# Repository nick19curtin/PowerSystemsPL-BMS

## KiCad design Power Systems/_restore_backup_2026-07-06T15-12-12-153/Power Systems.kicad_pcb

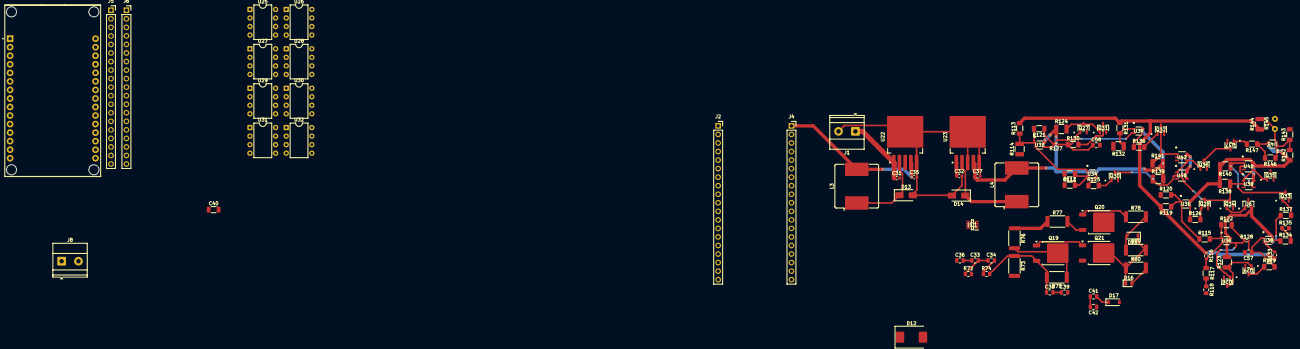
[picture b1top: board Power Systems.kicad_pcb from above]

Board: 2 copper layers, 113 parts (0 on the bottom side), 90 nets.

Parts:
C31, C32: 680uF; C_0603_1608Metric
C33, C34, C36, C38, C39, C41, C42: 0.1uF; C_0805_2012Metric
C35, C37: 220uF; C_0603_1608Metric
C40: 4.7uF; C_1206_3216Metric
C57, C58: 100nF; C_0805_2012Metric_Pad1.18x1.45mm_HandSolder
D12: SMCJ45A; D_SMC
D13, D14: SS34; D_SMA
D15: 1.25V; D_SOD-123
D16: D_Zener; D_0805_2012Metric
D17: D; D_SOD-123
IC1: INA296A3IDDFR; SOT65P280X110-8N
J1, J8: Conn_01x02; TerminalBlock_Phoenix_MKDS-1,5-2_1x02_P5.00mm_Horizontal
J2, J4, J5, J6: Conn_01x19; PinSocket_1x19_P2.54mm_Vertical
L3, L4: 33uH; L_Bourns_SRR1208_12.7x12.7mm
Q19, Q21: IRLR7843; TO-252-2
Q20: PMOS; TO-252-2
Q26, Q27, Q28, Q29, Q30, Q31, Q32, Q33, Q34, Q35, Q36, Q37: 2N7002; SOT-23TO-236_318-08_ONS-M
R72, R74: 100; R_0805_2012Metric
R73: 3.3M; R_2512_6332Metric
R75, R79, R80: 1M; R_2512_6332Metric
R76, R77: 10k; R_2512_6332Metric
R78: 1k; R_2512_6332Metric
R111: 1.5k; R_1206_3216Metric_Pad1.30x1.75mm_HandSolder
R112: 1.6k; R_1206_3216Metric_Pad1.30x1.75mm_HandSolder
R113, R131: 18k; R_1206_3216Metric_Pad1.30x1.75mm_HandSolder
R114, R123, R124, R132, R138, R139, R140, R141, R144: 10k; R_1210_3225Metric_Pad1.30x2.65mm_HandSolder
R115: 124K; R_1206_3216Metric_Pad1.30x1.75mm_HandSolder
R116, R133: 30k; R_0603_1608Metric_Pad0.98x0.95mm_HandSolder
R117, R134: 68k; R_1206_3216Metric_Pad1.30x1.75mm_HandSolder
R118, R135: 2k; R_0805_2012Metric_Pad1.20x1.40mm_HandSolder
R119: 50k; R_1206_3216Metric_Pad1.30x1.75mm_HandSolder
R120: 47k; R_1206_3216Metric_Pad1.30x1.75mm_HandSolder
R121: 390k; R_1206_3216Metric_Pad1.30x1.75mm_HandSolder
R122: 2Meg; R_1206_3216Metric_Pad1.30x1.75mm_HandSolder
R125, R126, R129, R130, R136, R137, R147: 220; R_1206_3216Metric_Pad1.30x1.75mm_HandSolder
R127, R128: 1k; R_0402_1005Metric_Pad0.72x0.64mm_HandSolder
R142: 13k; R_1206_3216Metric_Pad1.30x1.75mm_HandSolder
R143: 4.3k; R_1206_3216Metric_Pad1.30x1.75mm_HandSolder
R145: R_Variable; MF52C1103F3380_Thermistor-317-1376-ND-MF52C1103F3380
R146: 110k; R_1206_3216Metric_Pad1.30x1.75mm_HandSolder
U6: DS1812R-10+T&R; 21-0051H_MXM-M
U21: ESP32-DEVKIT-V1; MODULE_ESP32_DEVKIT_V1
U22: LM2596S-3.3; TO-263-5_TabPin3
U23: LM2596S-5; TO-263-5_TabPin3
U25, U26: LM358; DIP-8_W7.62mm
U27, U28, U29, U30, U31, U32: LM2903; DIP-8_W7.62mm
U33, U34, U35, U36, U37, U38, U43: LMV331; SC70-5_DCK_TEX-M
U39, U40, U41, U42: SN74AHC1G00DBVR; DBV5-M

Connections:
3.3v: C35.1, IC1.6 (VS), IC1.7 (REF1), J4.1, J6.1, L3.2, R111.2, R113.2, R116.1, R119.2, R131.1, R133.1, R144.1, U21.1 (3V3), U22.4 (FB)
5v: C37.1, L4.2, R76.1, R77.1, R123.2, R124.1, R138.2, R139.2, R140.2, R141.2, R142.1, U6.2 (VCC), U23.4 (FB), U33.5 (V+), U34.5 (V+), U35.5 (V+), U36.5 (V+), U37.5 (V+), U38.5 (V+), U39.5 (VCC), U40.5 (VCC), U41.5 (VCC), U42.5 (VCC), U43.5 (V+)
+12.6V: C31.2, C32.2, C33.1, C35.2, C36.2, C37.2, C39.2, C40.1, C40.2, C42.1, C57.2, C58.2, D12.1 (A1), D13.2 (A), D14.2 (A), D16.2 (A), D17.2 (A), IC1.2 (GND), IC1.3 (REF2), J1.2, J4.19, J6.19, J8.2, Q20.2 (G), Q21.3 (S), Q26.2 (S), Q27.2 (S), Q28.2 (S), Q29.2 (S), Q30.2 (S), Q31.2 (S), Q32.2 (S), Q33.2 (S), Q34.2 (S), Q35.2 (S), Q36.2 (S), Q37.2 (S), R72.2, R73.2, R80.2, R112.1, R114.1, R118.2, R120.1, R132.2, R135.2, R143.2, R145.2, U6.3 (GND), U21.2 (GND), U21.29 (GND), U22.3 (GND), U22.5 (~ON/OFF), U23.3 (GND), U23.5 (~ON/OFF), U25.4 (V-), U26.4 (V-), U27.4 (V-), U28.4 (V-), U29.4 (V-), U30.4 (V-), U31.4 (V-), U32.4 (V-), U33.2 (V-), U34.2 (V-), U35.2 (V-), U36.2 (V-), U37.2 (V-), U38.2 (V-), U39.3 (GND), U40.3 (GND), U41.3 (GND), U42.3 (GND), U43.2 (V-)
+15V: U25.8 (V+), U26.8 (V+), U27.8 (V+), U28.8 (V+), U29.8 (V+), U30.8 (V+), U31.8 (V+), U32.8 (V+)
/ALERT: J2.10, J5.10, U21.4 (D2)
/CHG_GATE: Q20.3 (S), R77.2
/Current/CHG_GATE: Q36.3 (D), Q37.3 (D)
/Current/CRESET: Q28.3 (D), Q30.3 (D), Q34.3 (D), R138.1, R139.1, U39.2 (B), U40.2 (B)
/Current/CSET: Q32.3 (D), R141.1, U42.1 (A)
/Current/DSET: Q33.3 (D), R140.1, U41.1 (A)
/Current/ISense_Out: R115.1, U33.3 (-), U34.1 (+), U35.3 (-)
/Current/V_TempSense: R144.2, R145.1, U43.3 (-)
/DSG_GATE: Q19.2 (G), R75.1, R76.2
/LOAD+: C31.1, C32.1, C41.2, D17.1 (K), J1.1, J8.1, U22.1 (VIN), U23.1 (VIN)
/SCL: J2.1, J5.1, U21.11 (D21)
/SDA: J4.10, J6.10, U21.14 (D22)
/SRN: C33.2, C34.1, IC1.1 (IN-), R72.1
/SRP: C34.2, C36.1, IC1.8 (IN+), R74.1
/Voltage/CELL 1: U26.6 (-), U29.6 (-)
/Voltage/CHG_GATE: U27.7, U28.7, U29.7, U30.7, U31.7, U32.7
/Voltage/OUT2: U26.7, U28.6 (-)
/Voltage/OUT3: U25.7, U27.6 (-)
/Voltage/VREF: U27.5 (+), U28.5 (+), U29.5 (+)
/Voltage/VREF_UV: U30.6 (-), U31.6 (-), U32.6 (-)
unnamed: C38.2, C39.1
unnamed: C41.1, C42.2
unnamed: D13.1 (K), L3.1, U22.2 (OUT)
unnamed: D14.1 (K), L4.1, U23.2 (OUT)
unnamed: D15.2 (A), R78.2, R79.1
unnamed: D15.1 (K), D16.1 (K), Q21.2 (G), R79.2, R80.1
unnamed: J5.2, U21.10 (D19)
unnamed: J5.3, U21.9 (D18)
unnamed: J5.4, U21.3 (D15)
unnamed: J5.5, U21.26 (D14)
unnamed: J5.6, U21.28 (D13)
unnamed: J5.7, U21.27 (D12)
unnamed: J5.8, U21.8 (D5)
unnamed: J5.9, U21.5 (D4)
unnamed: J5.15, U21.18 (VN)
unnamed: J5.16, U21.17 (VP)
unnamed: J5.18, U21.16 (EN)
unnamed: J5.19, U21.30 (VIN)
unnamed: J6.4, U21.12 (RX0)
unnamed: J6.5, U21.13 (TX0)
unnamed: J6.7, U21.6 (RX2)
unnamed: J6.8, U21.7 (TX2)
unnamed: J6.11, U21.15 (D23)
unnamed: J6.12, U21.23 (D25)
unnamed: J6.13, U21.24 (D26)
unnamed: J6.14, U21.25 (D27)
unnamed: J6.15, U21.21 (D32)
unnamed: J6.16, U21.22 (D33)
unnamed: J6.17, U21.20 (D35)
unnamed: J6.18, U21.19 (D34)
unnamed: Q19.1 (D), Q21.1 (D)
unnamed: C38.1, Q19.3 (S), R73.1, R74.2, R75.2
unnamed: Q20.1 (D), R78.1
unnamed: Q26.3 (D), Q29.1 (G), R123.1
unnamed: Q26.1 (G), R122.2, R128.1, U36.4
unnamed: Q27.3 (D), Q31.1 (G), R124.2
unnamed: Q27.1 (G), R121.1, R127.2, U33.4
unnamed: Q28.1 (G), R126.2
unnamed: Q29.3 (D), R129.1
unnamed: Q30.1 (G), R125.2
unnamed: Q31.3 (D), R130.2
unnamed: Q32.1 (G), R136.2
unnamed: Q33.1 (G), R137.2
unnamed: Q34.1 (G), U6.1 (RST)
unnamed: Q35.1 (G), U39.1 (A), U41.4 (Y)
unnamed: Q36.1 (G), U40.1 (A), U42.4 (Y)
unnamed: Q37.1 (G), R147.2
unnamed: R117.2, R118.1
unnamed: R125.1, U34.4
unnamed: R126.1, U35.4
unnamed: R134.2, R135.1
unnamed: R136.1, U37.4
unnamed: R137.1, U38.4
unnamed: R146.2, R147.1, U43.4
unnamed: R113.1, R114.2, R121.2, U33.1 (+)
unnamed: R111.1, R112.2, U34.3 (-)
unnamed: R119.1, R120.2, U35.1 (+)
unnamed: R115.2, R122.1, U36.1 (+)
unnamed: R116.2, R117.1, U36.3 (-)
unnamed: R131.2, R132.1, U37.1 (+)
unnamed: C58.1, R127.1, R130.1, U37.3 (-)
unnamed: C57.1, R128.2, R129.2, U38.1 (+)
unnamed: R133.2, R134.1, U38.3 (-)
unnamed: U39.4 (Y), U41.2 (B)
unnamed: U40.4 (Y), U42.2 (B)
unnamed: R142.2, R143.1, R146.1, U43.1 (+)

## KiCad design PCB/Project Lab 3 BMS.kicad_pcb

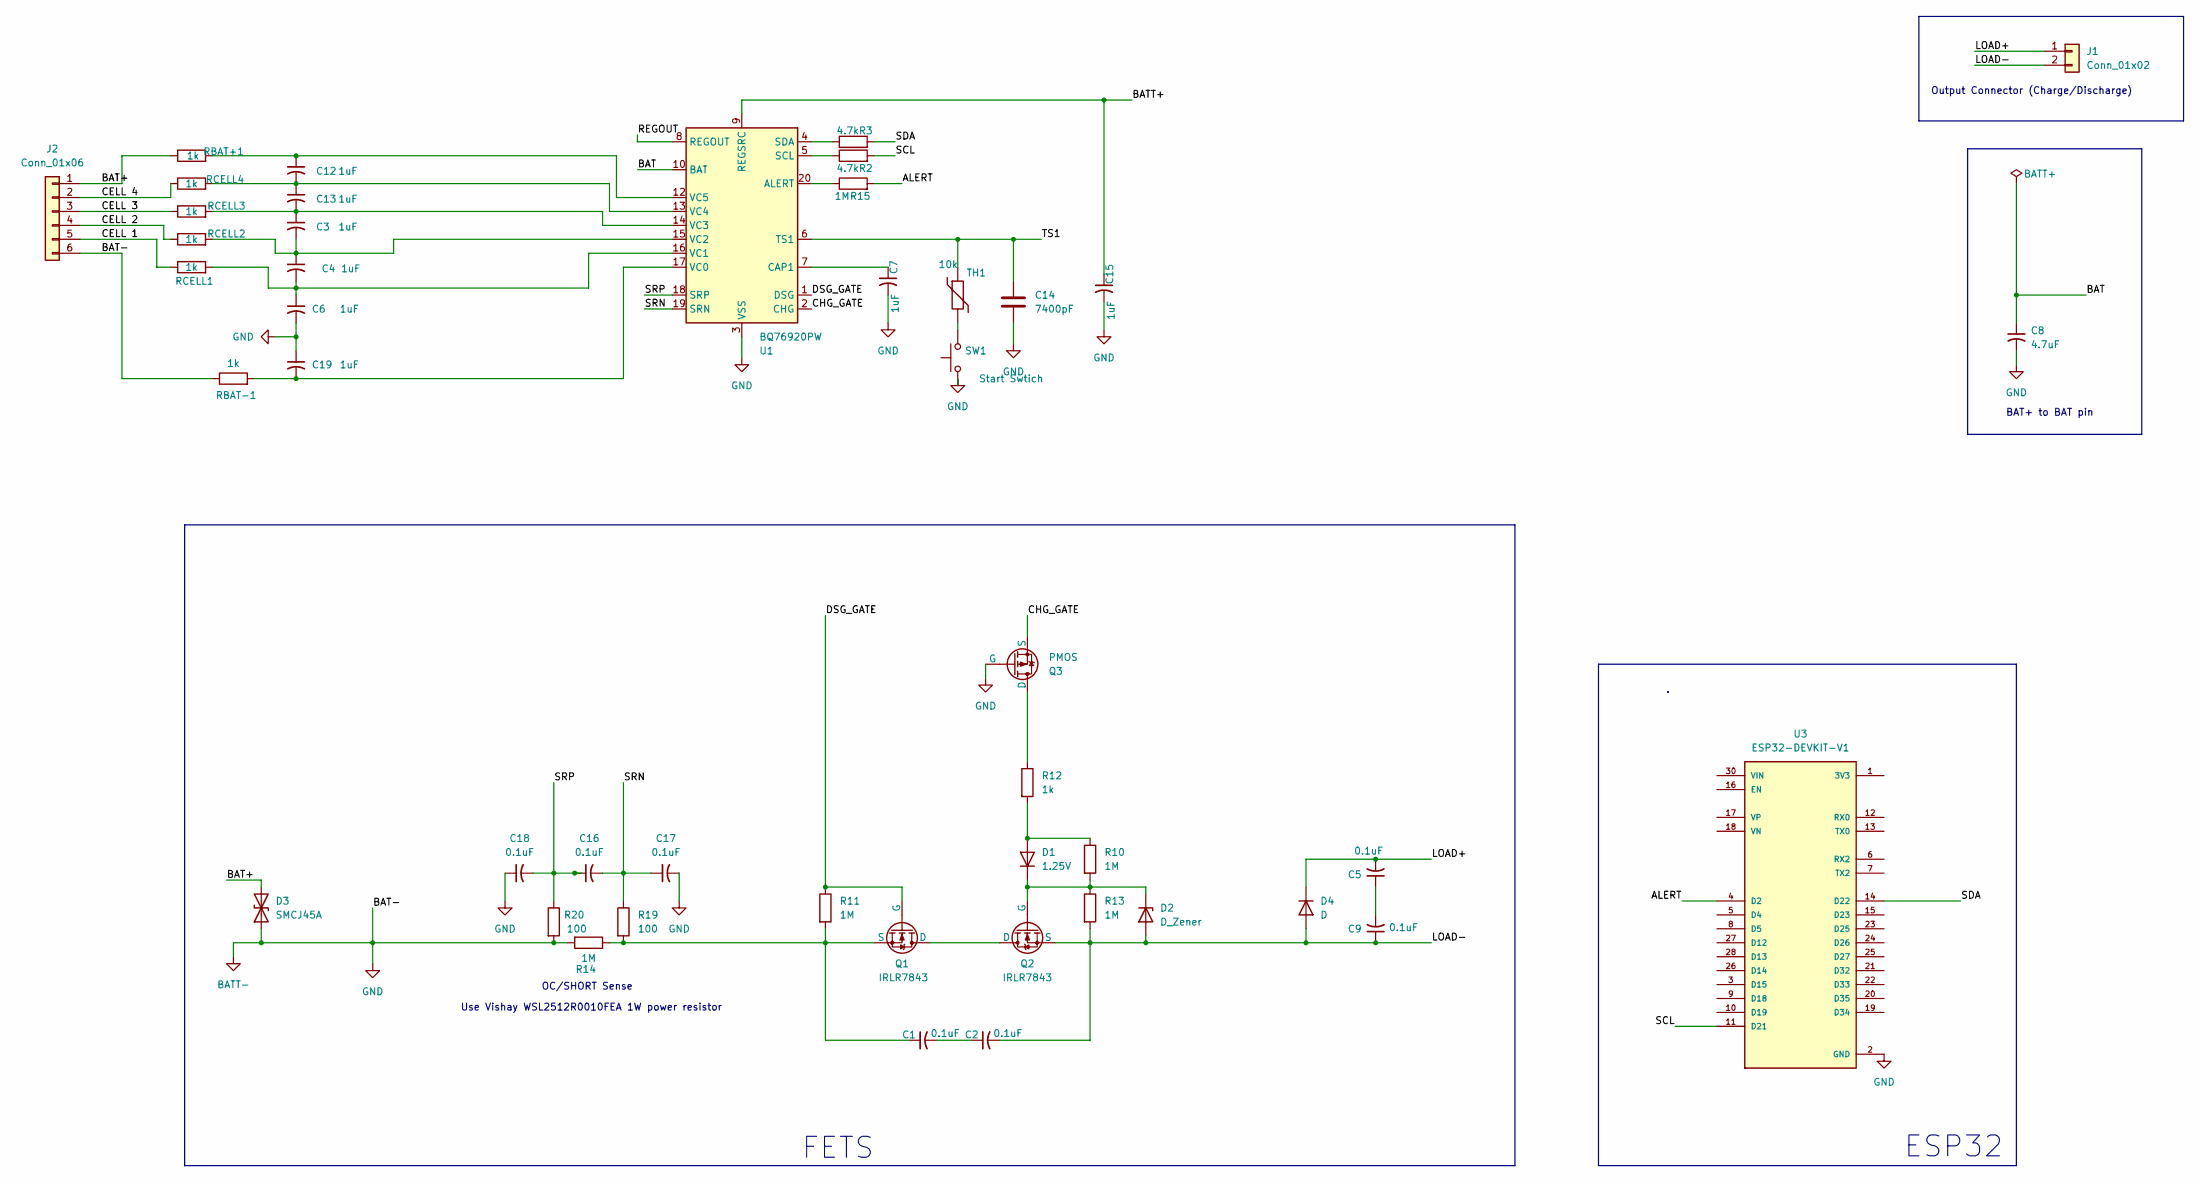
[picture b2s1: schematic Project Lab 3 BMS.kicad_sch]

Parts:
C1, C2, C5, C9, C16, C17, C18: 0.1uF; C_0805_2012Metric
C3, C4, C6, C7, C12, C13, C15, C19: 1uF; C_0805_2012Metric
C8: 4.7uF; C_1206_3216Metric
C14: 7400pF; C_0805_2012Metric
D1: 1.25V; D_SOD-123
D2: D_Zener; D_0201_0603Metric
D3: SMCJ45A; D_SMC
D4: D; D_SOD-123
J1: Conn_01x02; TerminalBlock_Phoenix_MKDS-1,5-2_1x02_P5.00mm_Horizontal
J2: Conn_01x06; JST_XH_B6B-XH-A_1x06_P2.50mm_Vertical
Q1, Q2: IRLR7843; TO-252-2
Q3: PMOS; TO-252-2
R2, R3: 4.7k; C_0805_2012Metric
R10, R11, R13, R14, R15: 1M; R_2512_6332Metric
R12: 1k; R_2512_6332Metric
R19, R20: 100; R_0805_2012Metric
RBAT+1: 1k; R_0805_2012Metric
RBAT-1: 1k; R_0805_2012Metric
RCELL1, RCELL2, RCELL3: 1k; C_0805_2012Metric
RCELL4: 1k; R_0805_2012Metric
SW1: Start Swtich; SW_SPST_PTS645Sx43SMTR92
TH1: 10k; R_0805_2012Metric
U1: BQ76920PW; TSSOP-20_4.4x6.5mm_P0.65mm
U3: ESP32-DEVKIT-V1; MODULE_ESP32_DEVKIT_V1; PARTREV N/A

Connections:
/<NO NET>: J2.5, RCELL1.1
/ALERT: R15.2, U3.4 (D2)
/BAT: C8.1, U1.10 (BAT)
/BAT+: D3.2 (A2), J2.1, RBAT+1.1
/BATT+: C15.1, U1.9 (REGSRC)
/CELL 2: J2.4, RCELL2.1
/CELL 3: J2.3, RCELL3.1
/CELL 4: J2.2, RCELL4.1
/CHG_GATE: Q3.3 (S), U1.2 (CHG)
/DSG_GATE: Q1.2 (G), R11.1, U1.1 (DSG)
/LOAD+: C5.2, D4.1 (K), J1.1
/LOAD-: C2.2, C9.1, D2.2 (A), D4.2 (A), J1.2, Q2.3 (S), R13.2
/REGOUT: U1.8 (REGOUT)
/SCL: R2.2, U3.11 (D21)
/SDA: R3.2, U3.14 (D22)
/SRN: C16.2, C17.1, R19.1, U1.19 (SRN)
/SRP: C16.1, C18.2, R20.1, U1.18 (SRP)
/TS1: C14.1, TH1.1, U1.6 (TS1)
BATT-: C6.2, C7.2, C8.2, C14.2, C15.2, C17.2, C18.1, C19.1, D3.1 (A1), J2.6, Q3.2 (G), R14.2, R20.2, RBAT-1.1, SW1.1, U1.3 (VSS), U3.2 (GND), U3.29 (GND)
unnamed: C1.2, C2.1
unnamed: C5.1, C9.2
unnamed: D1.2 (A), R10.1, R12.2
unnamed: D1.1 (K), D2.1 (K), Q2.2 (G), R10.2, R13.1
unnamed: Q1.1 (D), Q2.1 (D)
unnamed: C1.1, Q1.3 (S), R11.2, R14.1, R19.2
unnamed: Q3.1 (D), R12.1
unnamed: SW1.2, TH1.2
unnamed: R15.1, U1.20 (ALERT)
unnamed: C7.1, U1.7 (CAP1)
unnamed: R2.1, U1.5 (SCL)
unnamed: R3.1, U1.4 (SDA)
unnamed: C19.2, RBAT-1.2, U1.17 (VC0)
unnamed: C4.2, C6.1, RCELL1.2, U1.16 (VC1)
unnamed: C3.2, C4.1, RCELL2.2, U1.15 (VC2)
unnamed: C3.1, C13.2, RCELL3.2, U1.14 (VC3)
unnamed: C12.2, C13.1, RCELL4.2, U1.13 (VC4)
unnamed: C12.1, RBAT+1.2, U1.12 (VC5)

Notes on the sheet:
BAT+ to BAT pin
ESP32
OC/SHORT Sense
Use Vishay WSL2512R0010FEA 1W power resistor
Output Connector (Charge/Discharge)
FETS

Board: 2 copper layers, 46 parts (0 on the bottom side), 36 nets, no tracks yet.

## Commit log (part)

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2026-06-05 PCB Design Files
2026-06-05 update again
2026-06-09 Footprints Assigned
2026-06-09 AHHHHHJHHHHHHHHH
2026-06-23 Changed IC for Monitoring
